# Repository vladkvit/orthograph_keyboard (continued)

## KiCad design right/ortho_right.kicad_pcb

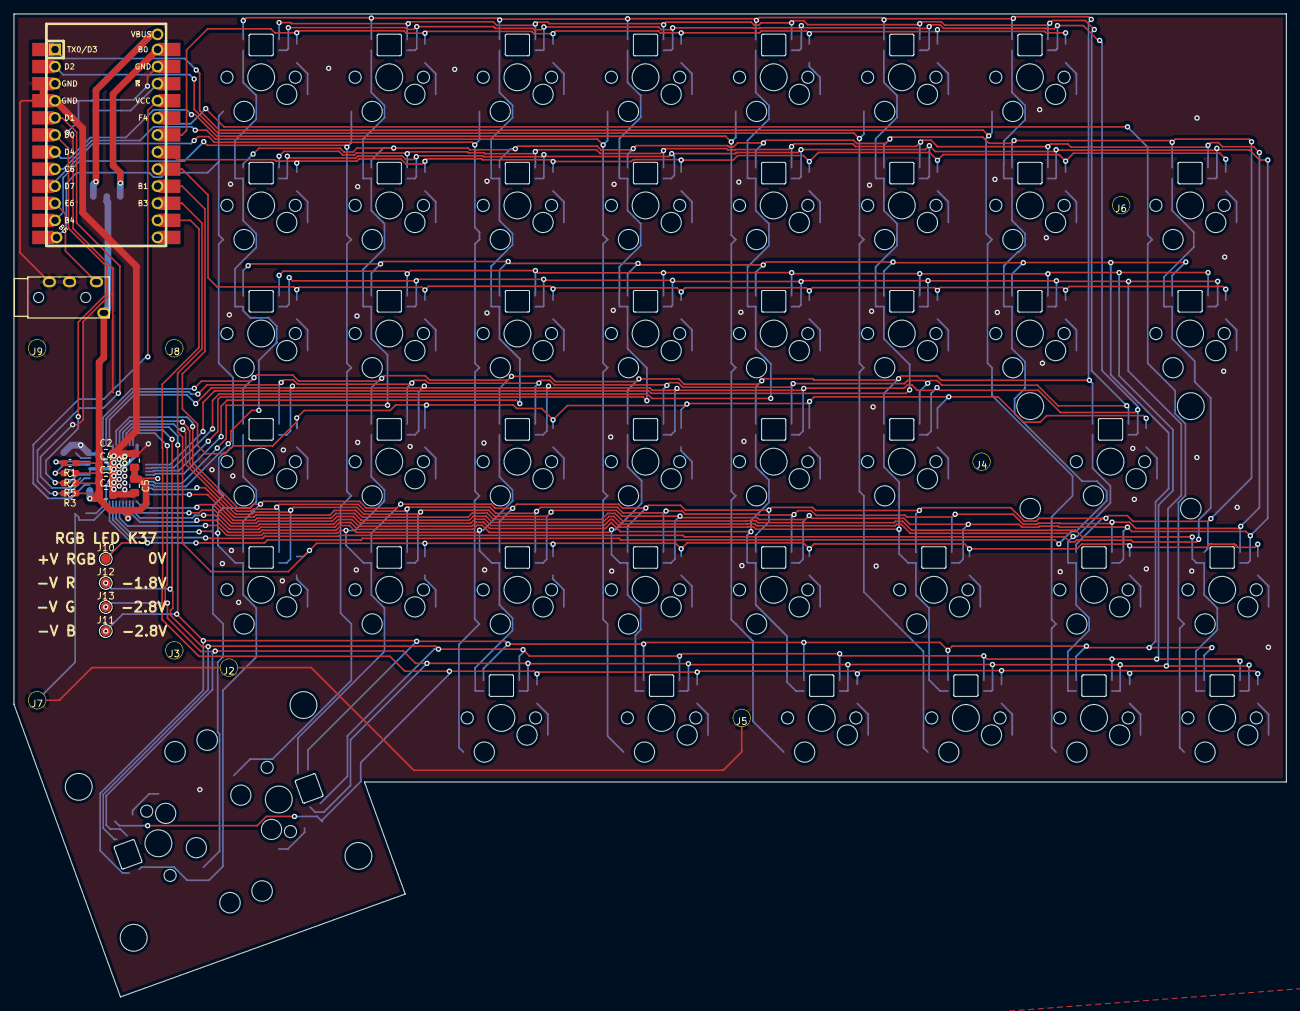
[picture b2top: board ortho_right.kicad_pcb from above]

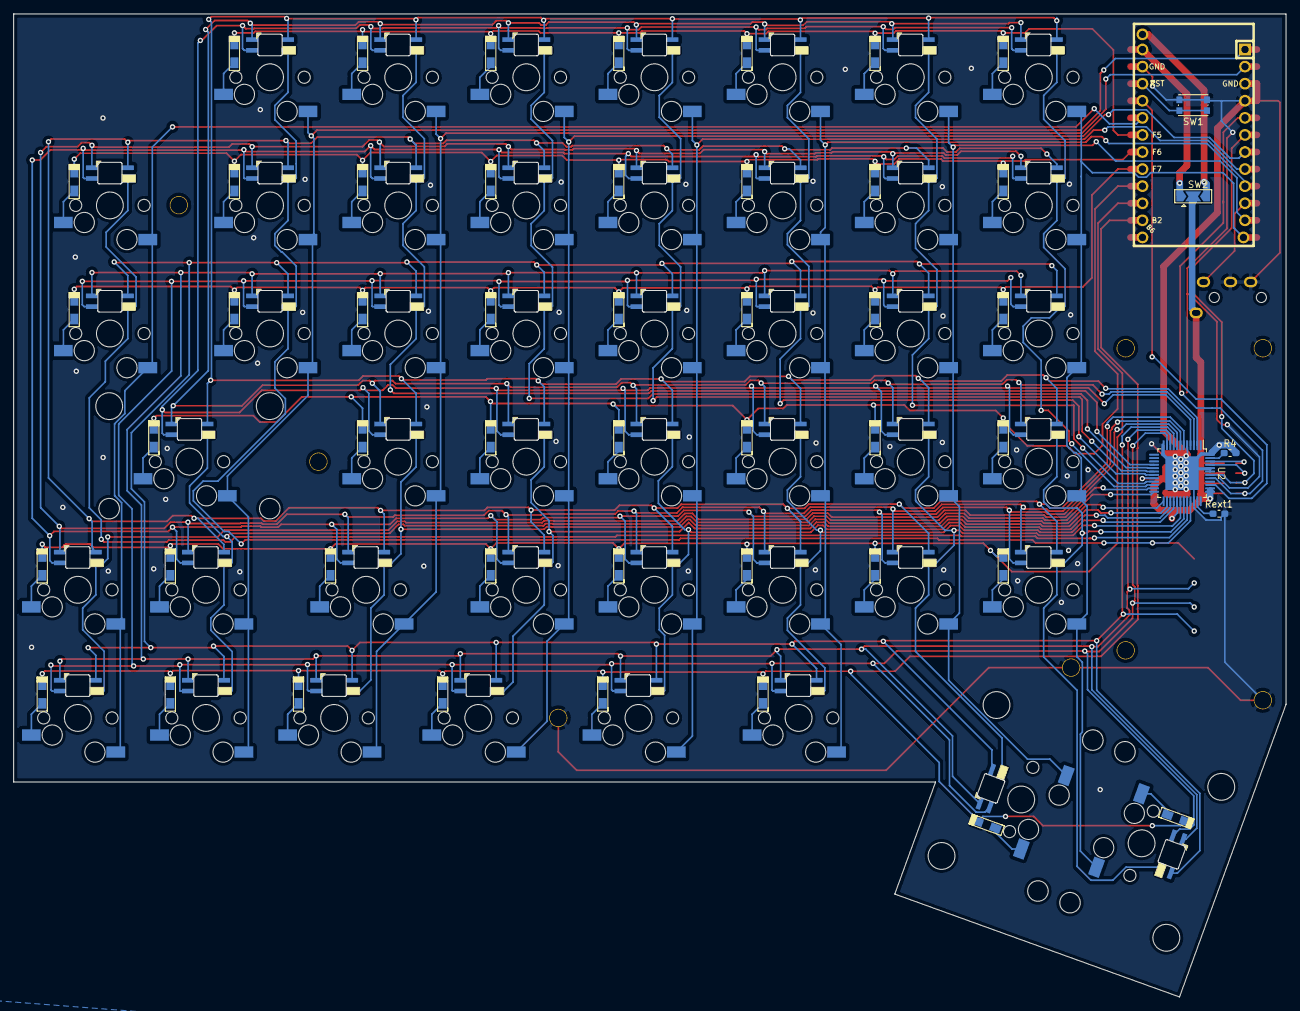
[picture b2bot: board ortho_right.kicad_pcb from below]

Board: 2 copper layers, 189.1 x 146.1 mm, 75 parts (5 on the bottom side), 98 nets.

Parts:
C1, C2, C3, C4, C5, C6: CP; C_0805_2012Metric_Pad1.15x1.40mm_HandSolder
J1: AudioJack4; TRRS-PJ-320A
J2, J3, J4, J5, J6, J7, J8, J9: Conn_01x01; m2.5_hole
J10, J11, J12, J13: Conn_01x01; TestPoint_Pad_D1.5mm
K11, K12, K13, K14, K15, K16, K17, K21, K22, K23, K24, K25, K26, K27, K31, K32, K33, K34, K35, K36, K37, K41, K42, K43, K44, K45, K46, K51, K52, K53, K54, K55, K57, K58, K66, K67, K68: KEYSW_RGB; Hybrid_PCB_100H_hotswap_diode_RGB_rot
K28, K38, K56: KEYSW_RGB; Hybrid_PCB_150H_hotswap_diode_RGB_rot
K47: KEYSW_RGB; Hybrid_PCB_225H_hotswap_diode_RGB
K61, K62: KEYSW_RGB; Hybrid_PCB_200H_hotswap_diode_RGB
K63, K64, K65: KEYSW_RGB; Hybrid_PCB_125H_hotswap_diode_RGB_rot
R1, R2, R4: R100k; R_0603_1608Metric_Pad1.05x0.95mm_HandSolder
R3, R5: R1k; R_0603_1608Metric_Pad1.05x0.95mm_HandSolder
Rext1: R20k; R_0603_1608Metric_Pad1.05x0.95mm_HandSolder
SW1: SW_PUSH_RESET; SW_Push_1P1T_NO_CK_KMR2
SW2: SW_SPDT_MSM; SolderJumper-3_P2.0mm_Open_TrianglePad1.0x1.5mm
U1: EliteC; Elite-C-castellated-24pin-holes
U2: IS31FL3733-TQ; TQFP-48-1EP_7x7mm_P0.5mm_EP5x5mm

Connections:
GND: C1.2, C2.2, C3.2, C4.2, C5.2, C6.2, J1.R2, J1.S, J2.1, J5.1, J7.1, J9.1, R4.2, Rext1.2, SW1.2, U1.3, U1.4, U1.23, U2.5, U2.12, U2.34, U2.43, U2.44, U2.48, U2.49
INTB: R2.2, U2.45
unnamed: K11.2, K11.4
unnamed: K12.2, K12.4
unnamed: K13.2, K13.4
unnamed: K14.2, K14.4
unnamed: K15.2, K15.4
unnamed: K16.2, K16.4
unnamed: K17.2, K17.4
unnamed: K21.2, K21.4
unnamed: K22.2, K22.4
unnamed: K23.2, K23.4
unnamed: K24.2, K24.4
unnamed: K25.2, K25.4
unnamed: K26.2, K26.4
unnamed: K27.2, K27.4
unnamed: K28.2, K28.4
unnamed: K31.2, K31.4
unnamed: K32.2, K32.4
unnamed: K33.2, K33.4
unnamed: K34.2, K34.4
unnamed: K35.2, K35.4
unnamed: K36.2, K36.4
unnamed: K37.2, K37.4
unnamed: K38.2, K38.4
unnamed: K41.2, K41.4
unnamed: K42.2, K42.4
unnamed: K43.2, K43.4
unnamed: K44.2, K44.4
unnamed: K45.2, K45.4
unnamed: K46.2, K46.4
unnamed: K47.2, K47.4
unnamed: K51.2, K51.4
unnamed: K52.2, K52.4
unnamed: K53.2, K53.4
unnamed: K54.2, K54.4
unnamed: K55.2, K55.4
unnamed: K56.2, K56.4
unnamed: K57.2, K57.4
unnamed: K58.2, K58.4
unnamed: K61.2, K61.4
unnamed: K62.2, K62.4
unnamed: K63.2, K63.4
unnamed: K64.2, K64.4
unnamed: K65.2, K65.4
unnamed: K66.2, K66.4
unnamed: K67.2, K67.4
unnamed: K68.2, K68.4
unnamed: R4.1, U2.47
unnamed: Rext1.1, U2.35
unnamed: SW1.1, U1.22
unnamed: SW2.1, U1.24
unnamed: SW2.3, U1.30
SCL: R5.2, U1.6, U2.42
SDA: R3.2, U1.5, U2.41
SDB: R1.2, U2.46
VCC: C1.1, C2.1, C3.1, C4.1, C5.1, C6.1, J1.T, R1.1, R2.1, R3.1, R5.1, SW2.2, U2.20, U2.29, U2.37, U2.38
VIO: U1.21, U2.39
col1: K11.1, K21.1, K31.1, K41.1, K51.1, K61.1, U1.12
col2: K12.1, K22.1, K32.1, K42.1, K52.1, K62.1, U1.11
col3: K13.1, K23.1, K33.1, K43.1, K53.1, K63.1, U1.9
col4: K14.1, K24.1, K34.1, K44.1, K54.1, K64.1, U1.8
col5: K15.1, K25.1, K35.1, K45.1, K55.1, K65.1, U1.7
col6: K16.1, K26.1, K36.1, K46.1, K56.1, K66.1, U1.2
col7: K17.1, K27.1, K37.1, K47.1, K57.1, K67.1, U1.1
col8: K28.1, K38.1, K58.1, K68.1, U1.20
led_col1: K11.5, K21.5, K31.5, U2.22
led_col2: K12.5, K22.5, K32.5, U2.21
led_col3: K13.5, K23.5, K33.5, U2.19
led_col4: K14.5, K24.5, K34.5, U2.18
led_col5: K15.5, K25.5, K35.5, U2.17
led_col6: K16.5, K26.5, K36.5, U2.16
led_col7: J10.1, K17.5, K27.5, K37.5, U2.33
led_col8: K28.5, K38.5, U2.32
led_col9: K41.5, K51.5, K61.5, U2.31
led_col10: K42.5, K52.5, K62.5, U2.30
led_col11: K43.5, K53.5, K63.5, U2.28
led_col12: K44.5, K54.5, K64.5, U2.27
led_col13: K45.5, K55.5, K65.5, U2.26
led_col14: K46.5, K56.5, K66.5, U2.25
led_col15: K47.5, K57.5, K67.5, U2.24
led_col16: K58.5, K68.5, U2.23
led_row1A: K11.8, K12.8, K13.8, K14.8, K15.8, K16.8, K17.8, K41.8, K42.8, K43.8, K44.8, K45.8, K46.8, K47.8, U2.2
led_row1B: K11.7, K12.7, K13.7, K14.7, K15.7, K16.7, K17.7, K41.7, K42.7, K43.7, K44.7, K45.7, K46.7, K47.7, U2.3
led_row1C: K11.6, K12.6, K13.6, K14.6, K15.6, K16.6, K17.6, K41.6, K42.6, K43.6, K44.6, K45.6, K46.6, K47.6, U2.4
led_row2A: K21.8, K22.8, K23.8, K24.8, K25.8, K26.8, K27.8, K28.8, K51.8, K52.8, K53.8, K54.8, K55.8, K56.8, K57.8, K58.8, U2.6
led_row2B: K21.7, K22.7, K23.7, K24.7, K25.7, K26.7, K27.7, K28.7, K51.7, K52.7, K53.7, K54.7, K55.7, K56.7, K57.7, K58.7, U2.7
led_row2C: K21.6, K22.6, K23.6, K24.6, K25.6, K26.6, K27.6, K28.6, K51.6, K52.6, K53.6, K54.6, K55.6, K56.6, K57.6, K58.6, U2.8
led_row3A: J11.1, K31.8, K32.8, K33.8, K34.8, K35.8, K36.8, K37.8, K38.8, K61.8, K62.8, K63.8, K64.8, K65.8, K66.8, K67.8, K68.8, U2.9
led_row3B: J12.1, K31.7, K32.7, K33.7, K34.7, K35.7, K36.7, K37.7, K38.7, K61.7, K62.7, K63.7, K64.7, K65.7, K66.7, K67.7, K68.7, U2.10
led_row3C: J13.1, K31.6, K32.6, K33.6, K34.6, K35.6, K36.6, K37.6, K38.6, K61.6, K62.6, K63.6, K64.6, K65.6, K66.6, K67.6, K68.6, U2.11
row1: K11.3, K12.3, K13.3, K14.3, K15.3, K16.3, K17.3, U1.19
row2: K21.3, K22.3, K23.3, K24.3, K25.3, K26.3, K27.3, K28.3, U1.18
row3: K31.3, K32.3, K33.3, K34.3, K35.3, K36.3, K37.3, K38.3, U1.17
row4: K41.3, K42.3, K43.3, K44.3, K45.3, K46.3, K47.3, U1.16
row5: K51.3, K52.3, K53.3, K54.3, K55.3, K56.3, K57.3, K58.3, U1.15
row6: K61.3, K62.3, K63.3, K64.3, K65.3, K66.3, K67.3, K68.3, U1.14
serial: J1.R1, U1.10

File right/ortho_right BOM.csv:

Designator,Package,Quantity,Designation,Specs,Value
U2,TQFP-48-1EP_7x7mm_P0.5mm_EP5x5mm,1,IS31FL3733-TQ,,
Rext1,R_0603_1608Metric_Pad1.05x0.95mm_HandSolder,1,R20k,0.2W 1%,20k
"R5,R3",R_0603_1608Metric_Pad1.05x0.95mm_HandSolder,2,R1k,0.2W 5%,1k
"R4,R2,R1",R_0603_1608Metric_Pad1.05x0.95mm_HandSolder,3,R100k,0.2W 5%,100k
"C6,C5,C4,C3,C2,C1",C_0805_2012Metric_Pad1.15x1.40mm_HandSolder,6,CP,"Tantalum, 5V, any ESR, any %",0.1 microF
"K56A,K38A,K28A,K47A,K62A,K61A,K58A,K57A,K17A,K68A,K67A,K66A,K51A,K41A,K31A,K21A,K11A,K55A,K54A,K53A,K52A,K46A,K45A,K44A,K43A,K42A,K37A,K36A,K35A,K34A,K33A,K32A,K27A,K26A,K25A,K24A,K23A,K22A,K16A,K15A,K14A,K13A,K12A,K65A,K64A,K63A ",RGB LED,46,KEYSW_RGB,RGB LED,RGB3528 Face-up
"K56B,K38B,K28B,K47B,K62B,K61B,K58B,K57B,K17B,K68B,K67B,K66B,K51B,K41B,K31B,K21B,K11B,K55B,K54B,K53B,K52B,K46B,K45B,K44B,K43B,K42B,K37B,K36B,K35B,K34B,K33B,K32B,K27B,K26B,K25B,K24B,K23B,K22B,K16B,K15B,K14B,K13B,K12B,K65B,K64B,K63B ",Diode,46,KEYSW_RGB,Diode,1N4148W-TP
SW1,SW_Push_1P1T_NO_CK_KMR2,1,SW_PUSH_RESET,KMR231GLFS,
J1,TRRS-PJ-320A,1,AudioJack4,TRRS-PJ-320A,

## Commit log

2021-03-09 v0.1 prototype pcb, works well
2021-06-16 cache
2021-06-19 Updated schematic of left side split.
2021-06-20 Some initial work on the PCB update.
2021-06-20 More PCB updates
2021-06-21 More PCB stuff
2021-06-27 A bunch of changes to left half of PCB in order to make room for battery and various connectors. Also added a switch and extra connector on the schematic.
2021-06-27 Moved around components and placed the JST power connectors
2021-08-31 Lots of changes to left side of controller. Should be pretty close to rev2
2021-09-06 Minor updates
2022-06-20 Kicad 6 migration; other fixes
2024-07-21 Broke out keys into individual components so that the BOM and pick and place are easier to generate.
2025-03-23 Kicad 9 upgrade.
2025-03-25 Fix SDA/SCL bug
2025-12-19 checking stuff in
